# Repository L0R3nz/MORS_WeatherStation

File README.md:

# M.O.R.S.

This weather station is a passion-driven open-source project aimed at providing accurate monitoring of atmospheric conditions. Please note that as a hobby project, it may contain errors or limitations in functionality. However, I will do my best to continuously improving and refining the station's capabilities.

# Links
1. [Project Requirements](doc/Requirements.md)
2. [Sensors Evaluation](doc/Sensors.md)
3. [Hardware Documentation](doc/Hardware.md)

______________________________________________________
M.O.R.S project is based on opensource [tools](doc/Tools.md)

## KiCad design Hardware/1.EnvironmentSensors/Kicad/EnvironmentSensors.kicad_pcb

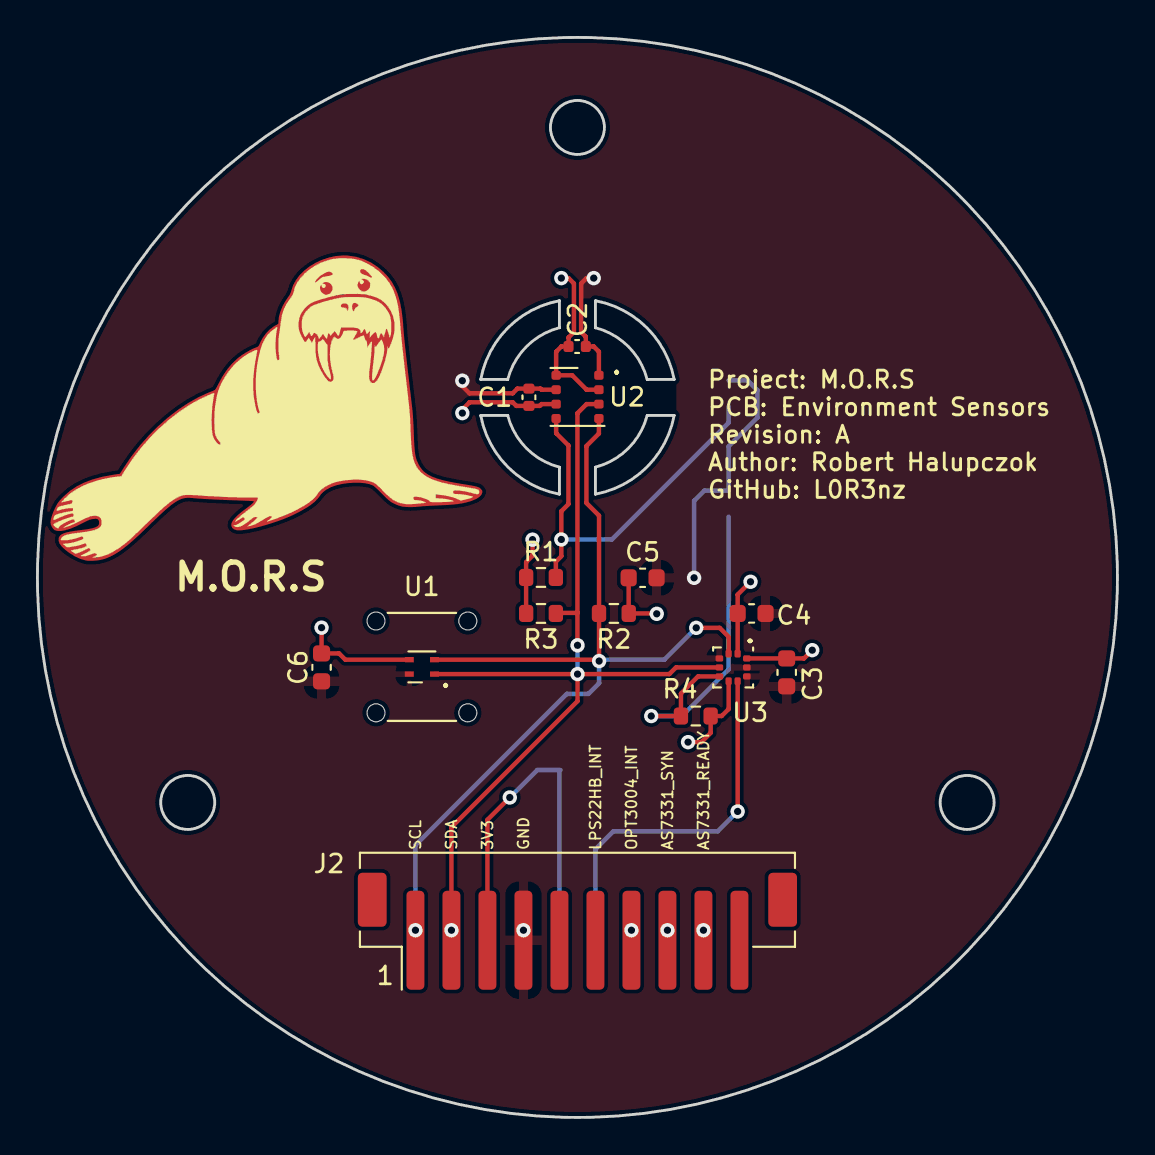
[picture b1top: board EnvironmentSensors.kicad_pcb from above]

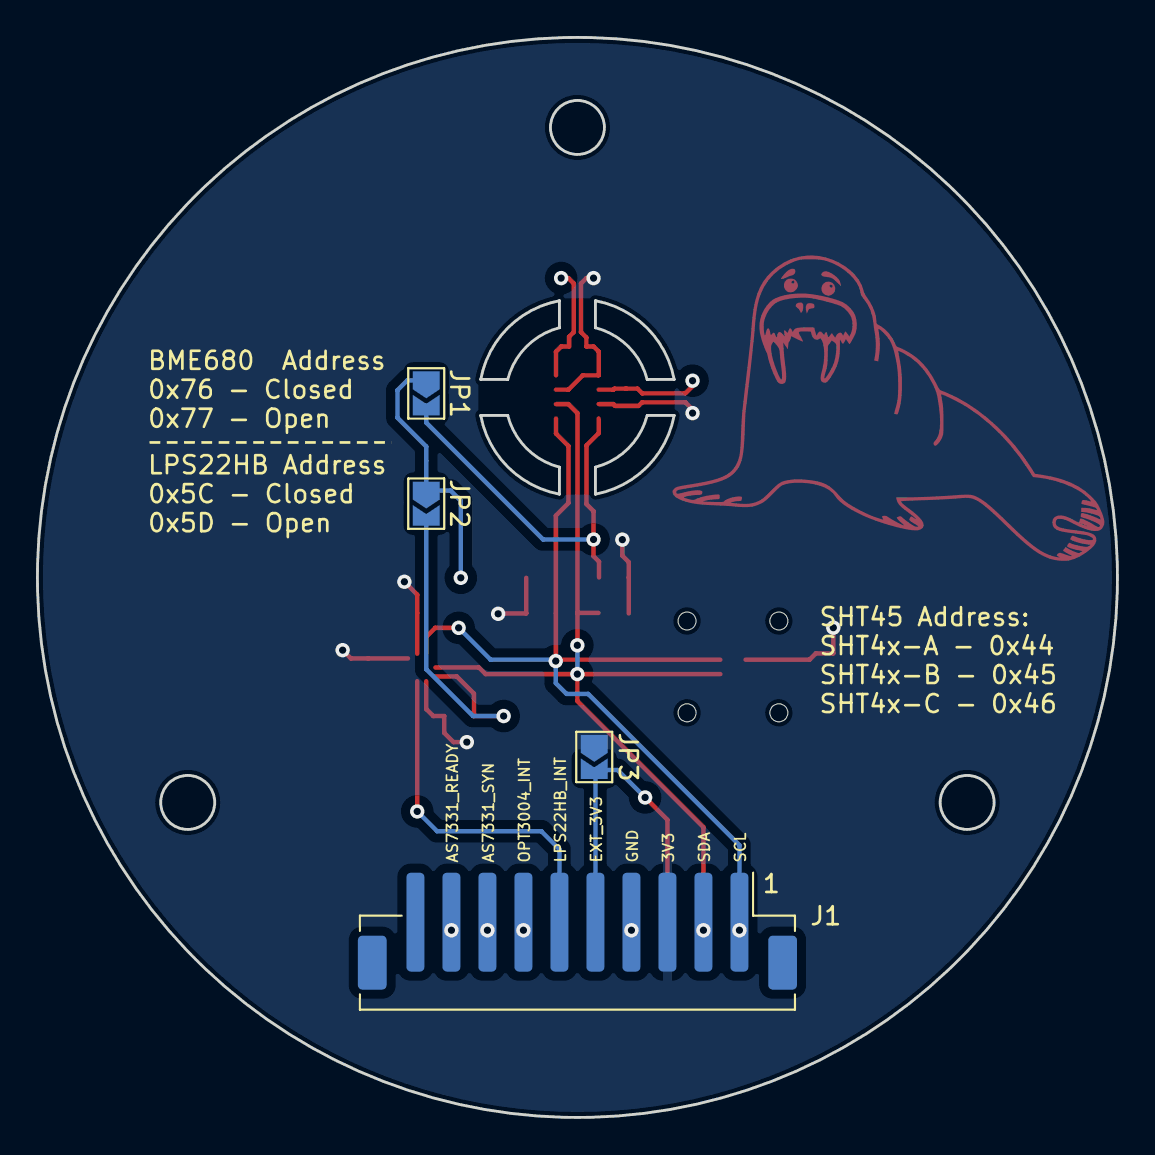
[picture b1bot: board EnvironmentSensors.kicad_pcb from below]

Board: 2 copper layers, 60.0 x 60.0 mm, 19 parts (4 on the bottom side), 11 nets.

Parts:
C1, C2: 100n; C_0402_1005Metric
C3, C5, C6: 100n; C_0603_1608Metric
C4: 4.7uF; C_0603_1608Metric
FL1: Sht45 Filter; FIL_SF2_FILTER_CAP
J1, J2: Conn_01x10_Pin; JST_PH_B10B-PH-SM4-TB_1x10-1MP_P2.00mm_Vertical
JP1, JP2, JP3: SolderJumper_2_Open; SolderJumper-2_P1.3mm_Open_TrianglePad1.0x1.5mm
R1, R4: 10k; R_0603_1608Metric
R2, R3: 4.7k; R_0603_1608Metric
U1: SHT4x; Sensirion_DFN-4_1.5x1.5mm_P0.8mm_SHT4x_NoCentralPad
U2: BME680; Bosch_LGA-8_3x3mm_P0.8mm_ClockwisePinNumbering
U3: LPS22HB; ST_HLGA-10_2x2mm_P0.5mm_LayoutBorder3x2y

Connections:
+3.3V: C1.1, C2.1, C3.1, C4.1, C5.1, C6.1, J1.3, JP3.1 (A), R1.1, R2.1, R3.2, R4.1, U1.3 (VDD), U2.2 (CSB), U2.6 (VDDIO), U2.8 (VDD), U3.1 (Vdd_IO), U3.6 (~CS), U3.10 (VDD)
EXT_3V3: J1.5, J2.3, JP3.2 (B)
EXT_AS7331_READY: J1.9, J2.9
EXT_AS7331_SYN: J1.8, J2.8
EXT_OPT3004_INT: J1.7, J2.7
GND: C1.2, C2.2, C3.2, C4.2, C5.2, C6.2, J1.4, J2.4, JP1.1 (A), JP2.1 (A), U1.4 (VSS), U2.1 (GND), U2.7 (GND), U3.3 (RES), U3.8 (GND), U3.9 (GND)
I2C_SCL: J1.1, J2.1, R2.2, U1.2 (SCL), U2.4 (SCK), U3.2 (SCL)
I2C_SDA: J1.2, J2.2, R3.1, U1.1 (SDA), U2.3 (SDI), U3.4 (SDA)
LPS22HB_INT: J1.6, U3.7 (INT_DRDY)
unnamed: JP1.2 (B), R1.2, U2.5 (SDO)
unnamed: JP2.2 (B), R4.2, U3.5 (SA0)

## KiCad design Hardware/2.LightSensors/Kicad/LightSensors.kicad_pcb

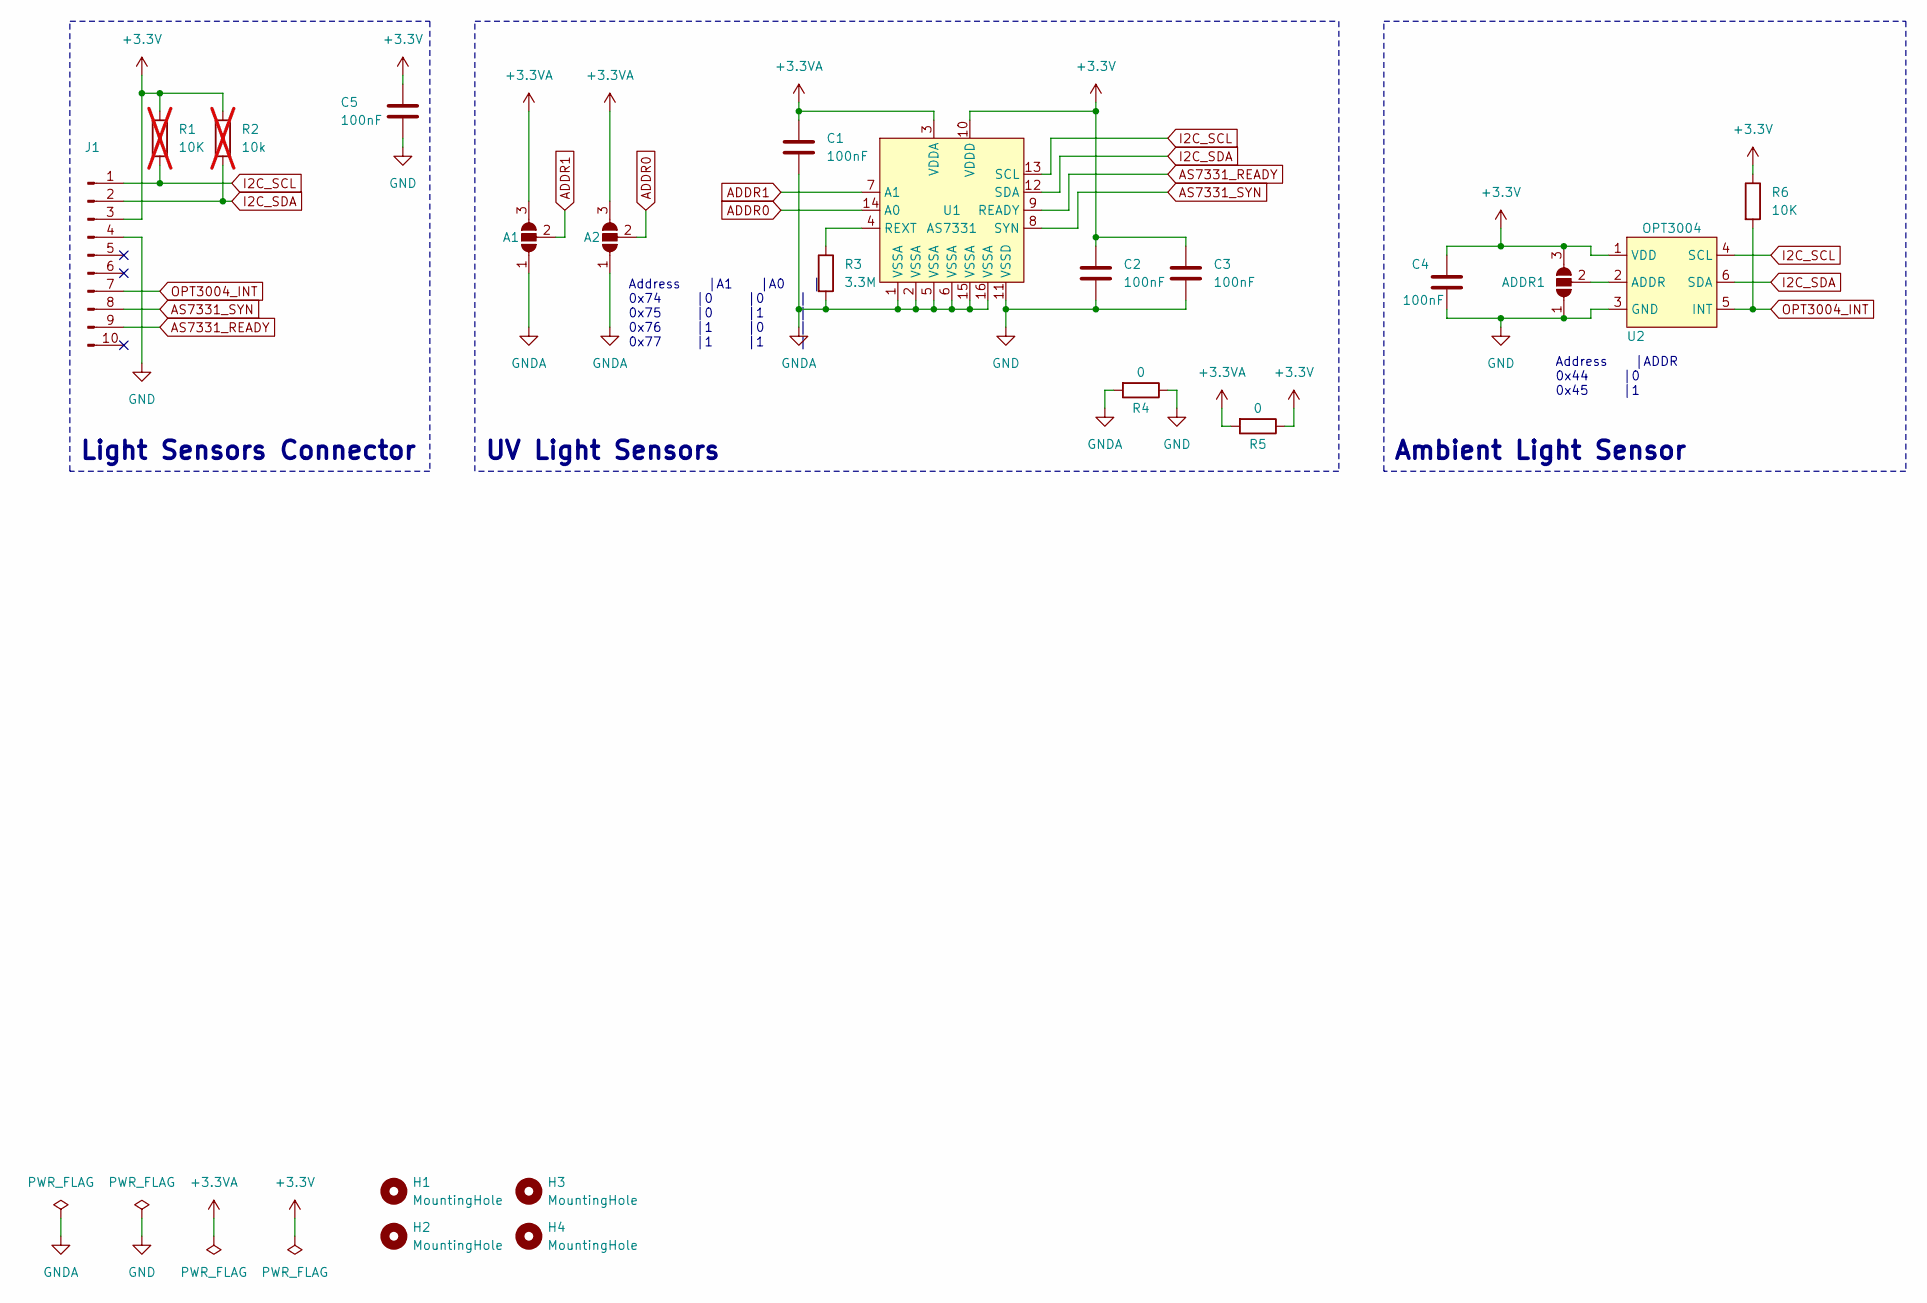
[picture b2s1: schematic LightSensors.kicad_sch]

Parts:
A1, A2: SolderJumper_3_Open; SolderJumper-3_P2.0mm_Open_TrianglePad1.0x1.5mm
ADDR1: SolderJumper_3_Open; SolderJumper-3_P2.0mm_Open_TrianglePad1.0x1.5mm
C1, C2, C3, C4, C5: 100nF; C_0603_1608Metric
H1, H2, H3, H4: MountingHole; MountingHole_2.2mm_M2
J1: Conn_01x10_Pin; JST_PH_B10B-PH-SM4-TB_1x10-1MP_P2.00mm_Vertical
R1: 10K; R_0603_1608Metric; not fitted
R2: 10k; R_0603_1608Metric; not fitted
R3: 3.3M; R_0603_1608Metric
R4, R5: 0; NetTie-2_THT_Pad0.3mm
R6: 10K; C_0603_1608Metric
U1: AS7331; OLGA-16
U2: OPT3004; SON65P200X200X65-7N

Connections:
+3.3V: ADDR1.3 (B), C2.1, C3.1, C4.1, C5.1, J1.3, R1.1, R2.1, R5.1, R6.1, U1.10 (VDDD), U2.1 (VDD)
+3.3VA: A1.3 (B), A2.3 (B), C1.1, R5.2, U1.3 (VDDA)
ADDR0: A2.2 (C), U1.14 (A0)
ADDR1: A1.2 (C), U1.7 (A1)
AS7331_READY: J1.9, U1.9 (READY)
AS7331_SYN: J1.8, U1.8 (SYN)
GND: ADDR1.1 (A), C2.2, C3.2, C4.2, C5.2, J1.4, R4.1, U1.11 (VSSD), U2.3 (GND)
GNDA: A1.1 (A), A2.1 (A), C1.2, R3.2, R4.2, U1.1 (VSSA), U1.2 (VSSA), U1.5 (VSSA), U1.6 (VSSA), U1.15 (VSSA), U1.16 (VSSA)
I2C_SCL: J1.1, R1.2, U1.13 (SCL), U2.4 (SCL)
I2C_SDA: J1.2, R2.2, U1.12 (SDA), U2.6 (SDA)
unnamed: ADDR1.2 (C), U2.2 (ADDR)
unnamed: R3.1, U1.4 (REXT)
OPT3004_INT: J1.7, R6.2, U2.5 (INT)

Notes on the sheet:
Light Sensors Connector
Address |A1 |A0 | 0x74 |0 |0 | 0x75 |0 |1 | 0x76 |1 |0 | 0x77 |1 |1 |
UV Light Sensors
Ambient Light Sensor
Address |ADDR 0x44 |0 0x45 |1

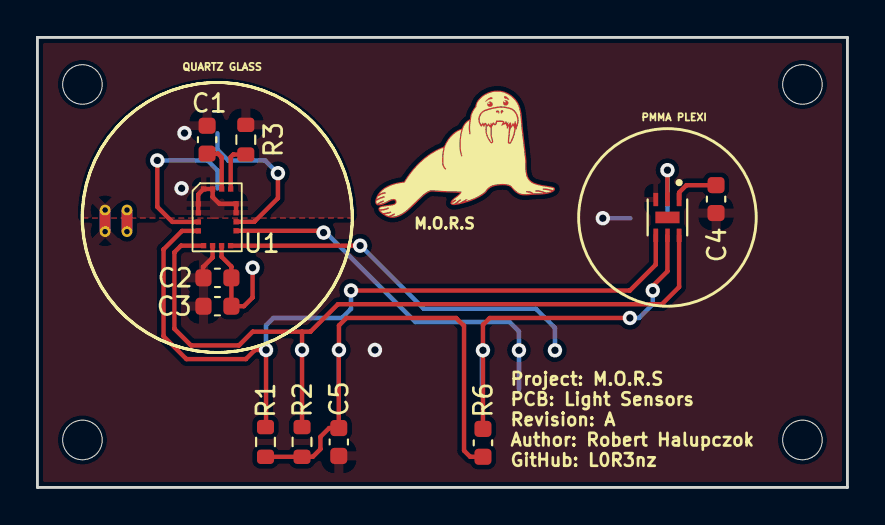
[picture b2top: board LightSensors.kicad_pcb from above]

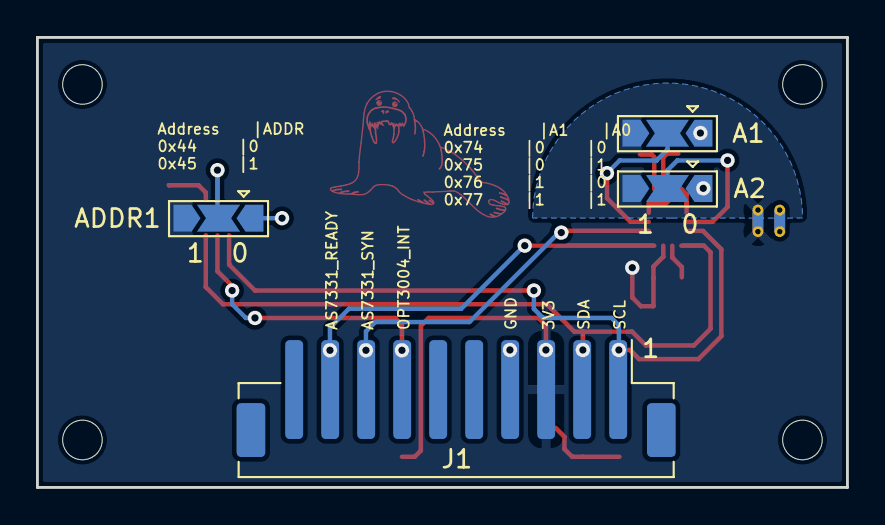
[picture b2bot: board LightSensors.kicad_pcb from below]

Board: 2 copper layers, 45.0 x 25.0 mm, 21 parts (5 on the bottom side), 13 nets.

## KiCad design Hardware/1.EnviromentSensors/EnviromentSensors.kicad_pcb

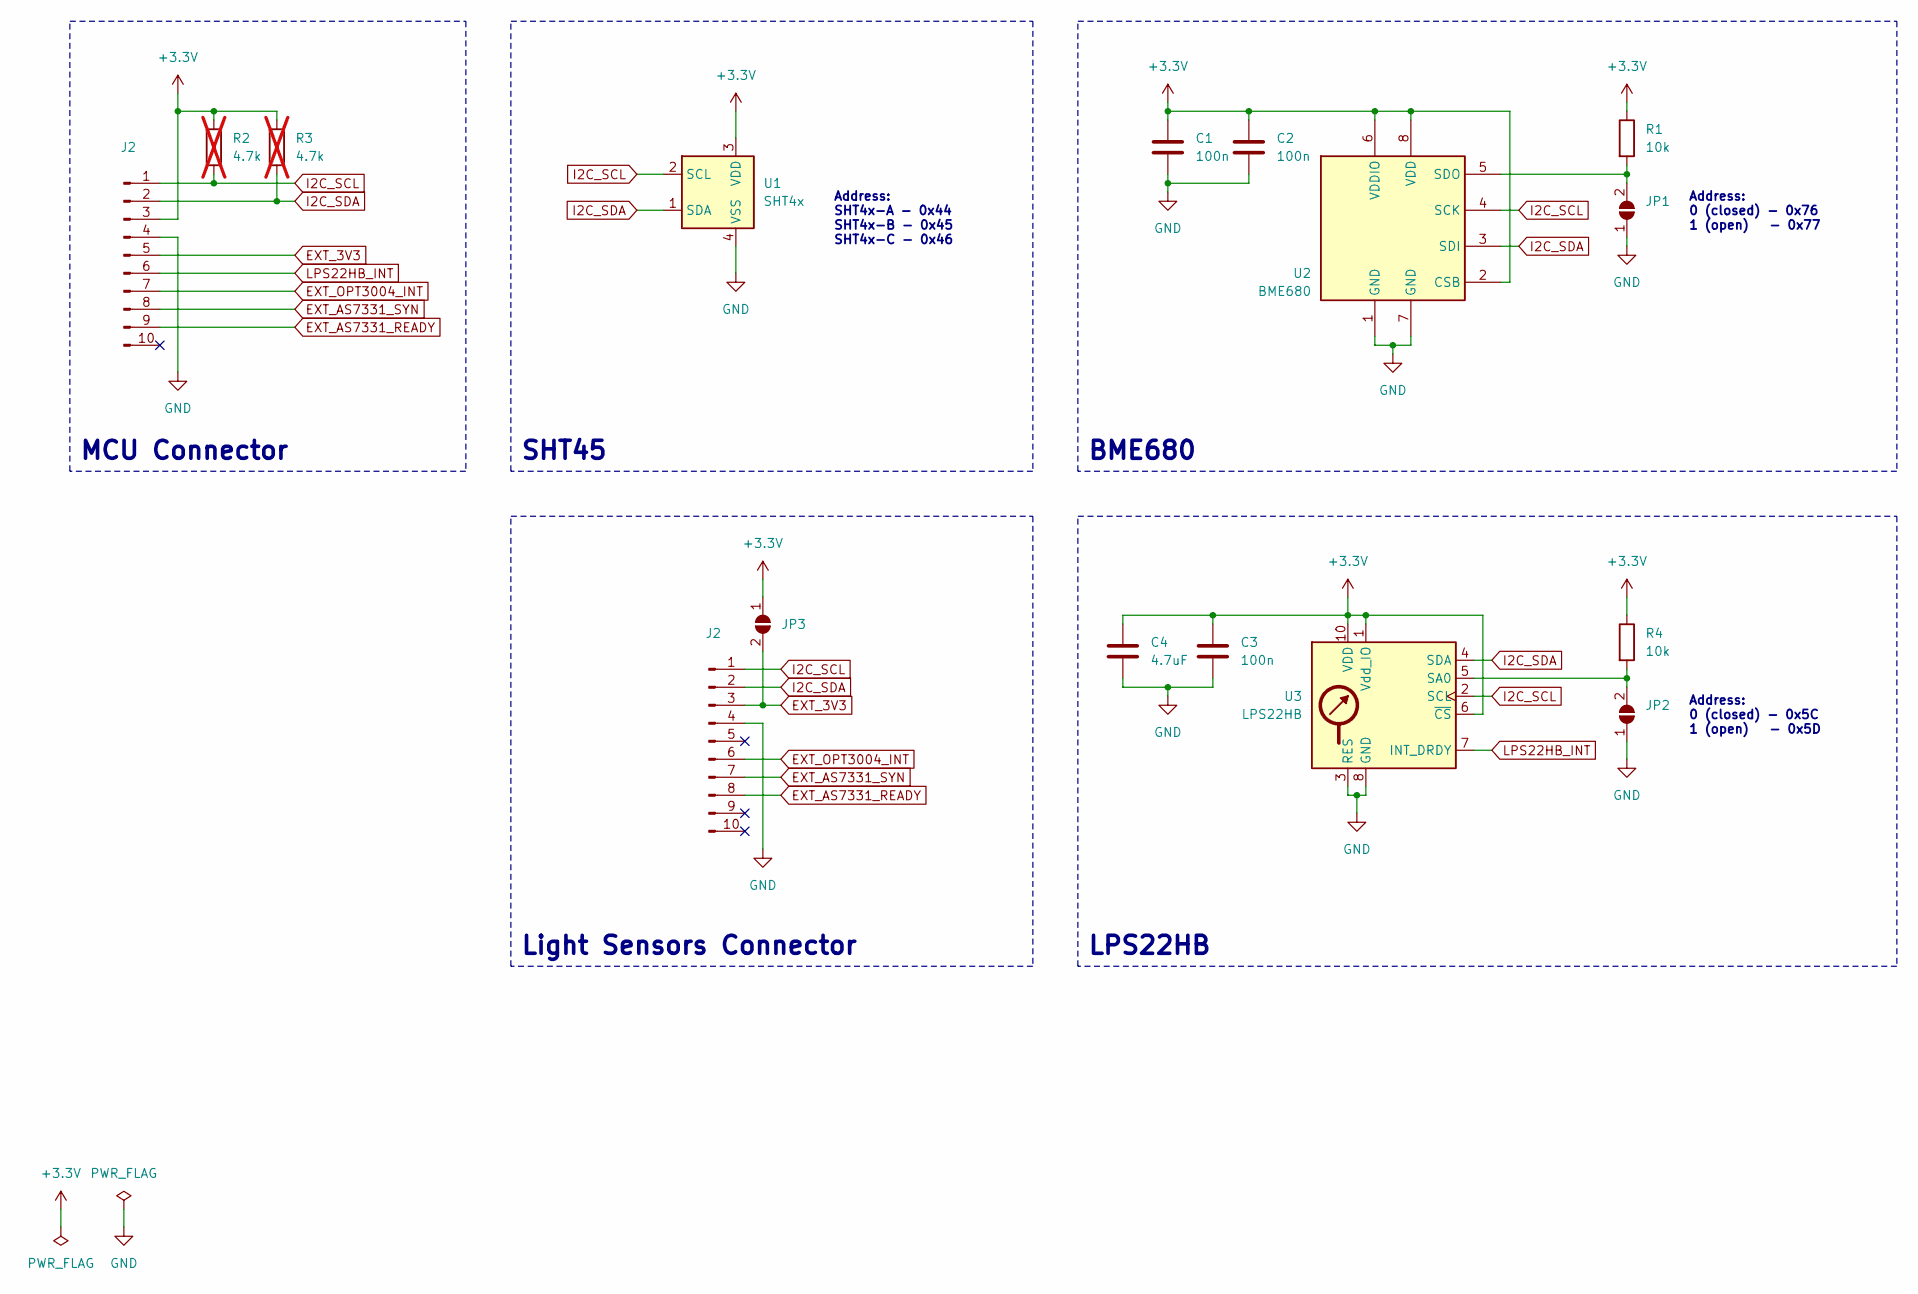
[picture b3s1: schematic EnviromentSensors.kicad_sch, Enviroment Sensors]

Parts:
C1, C2, C3: 100n; C_0402_1005Metric; MPN C77020
C4: 4.7uF; C_0402_1005Metric; MPN C2858031
J2: Conn_01x10_Pin; JST_PH_B10B-PH-K_1x10_P2.00mm_Vertical
JP1, JP2, JP3: SolderJumper_2_Open; SolderJumper-2_P1.3mm_Open_TrianglePad1.0x1.5mm
R1, R4: 10k; R_0402_1005Metric; MPN C25744
R2, R3: 4.7k; R_0402_1005Metric; MPN C25940; not fitted
U1: SHT4x; Sensirion_DFN-4_1.5x1.5mm_P0.8mm_SHT4x_NoCentralPad
U2: BME680; Bosch_LGA-8_3x3mm_P0.8mm_ClockwisePinNumbering; MPN C125972
U3: LPS22HB; ST_HLGA-10_2x2mm_P0.5mm_LayoutBorder3x2y; MPN C94049

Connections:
+3.3V: C1.1, C2.1, C3.1, C4.1, JP3.1 (A), R1.1, R2.1, R3.2, R4.1, U1.3 (VDD), U2.2 (CSB), U2.6 (VDDIO), U2.8 (VDD), U3.1 (Vdd_IO), U3.6 (~CS), U3.10 (VDD); also elsewhere on the board
EXT_3V3: JP3.2 (B); also elsewhere on the board
GND: C1.2, C2.2, C3.2, C4.2, JP1.1 (A), JP2.1 (A), U1.4 (VSS), U2.1 (GND), U2.7 (GND), U3.3 (RES), U3.8 (GND), U3.9 (GND); also elsewhere on the board
I2C_SCL: R2.2, U1.2 (SCL), U2.4 (SCK), U3.2 (SCL); also elsewhere on the board
I2C_SDA: R3.1, U1.1 (SDA), U2.3 (SDI), U3.4 (SDA); also elsewhere on the board
LPS22HB_INT: U3.7 (INT_DRDY); also elsewhere on the board
unnamed: JP1.2 (B), R1.2, U2.5 (SDO)
unnamed: JP2.2 (B), R4.2, U3.5 (SA0)

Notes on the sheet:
Address: 0 (closed) - 0x76 1 (open) - 0x77
Address: 0 (closed) - 0x5C 1 (open) - 0x5D
Address: SHT4x-A - 0x44 SHT4x-B - 0x45 SHT4x-C - 0x46
MCU Connector
BME680
LPS22HB
SHT45
Light Sensors Connector

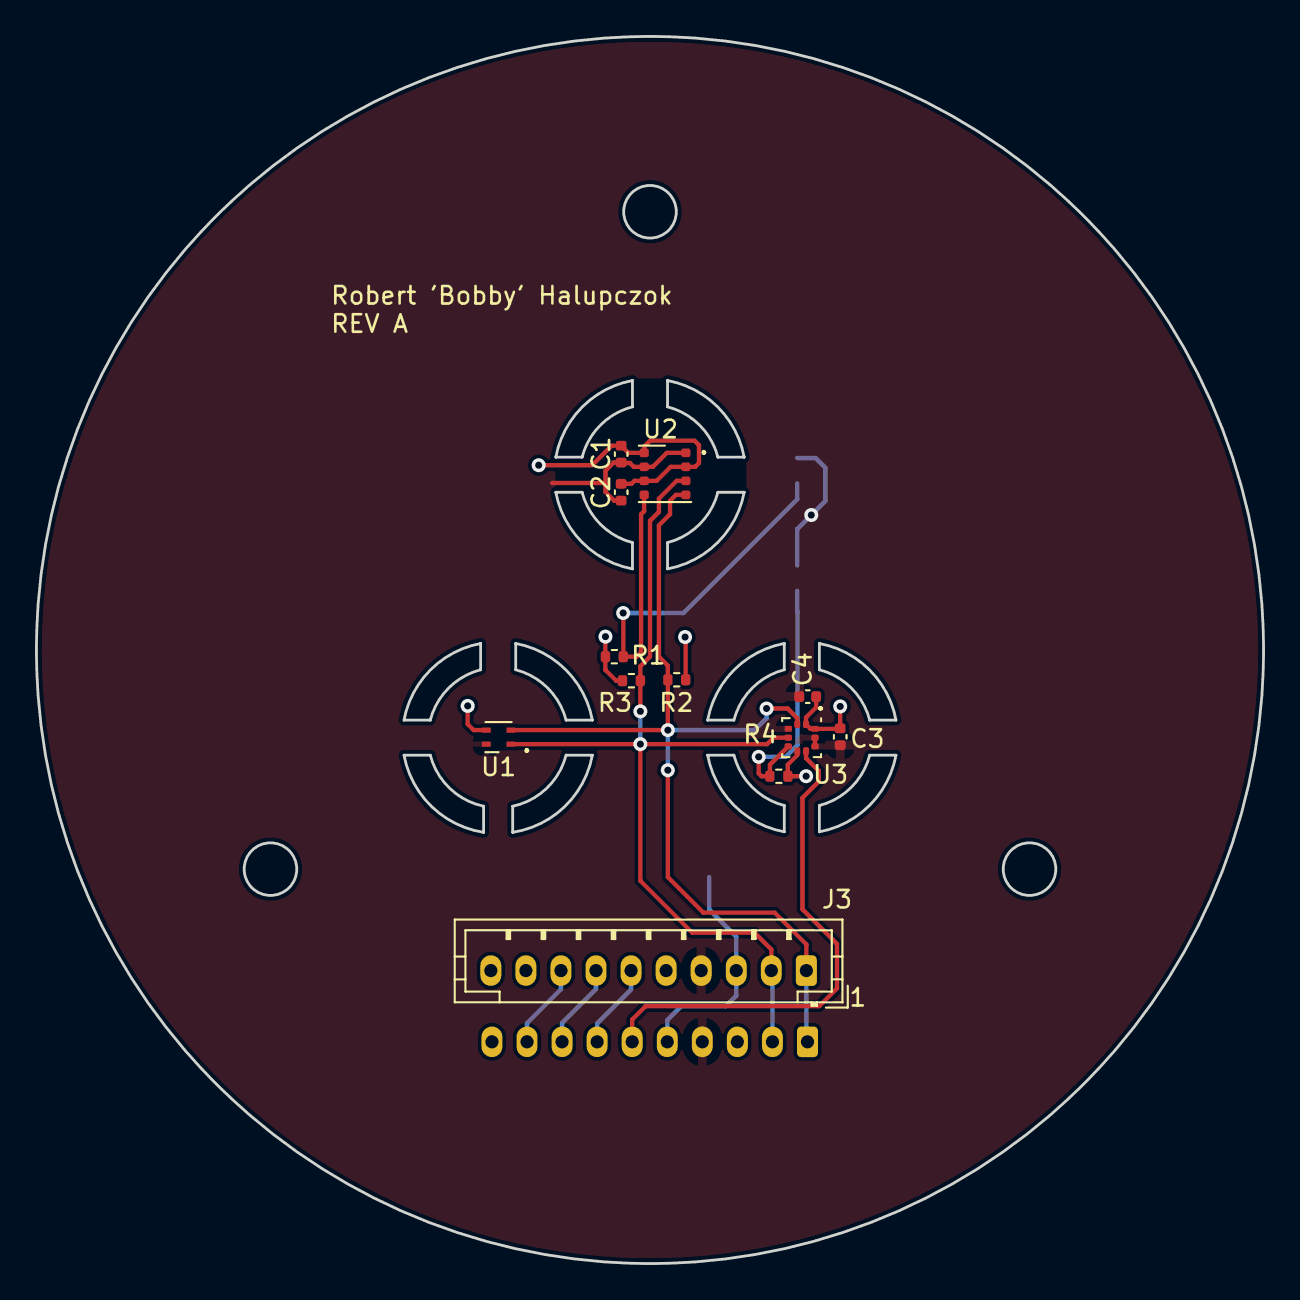
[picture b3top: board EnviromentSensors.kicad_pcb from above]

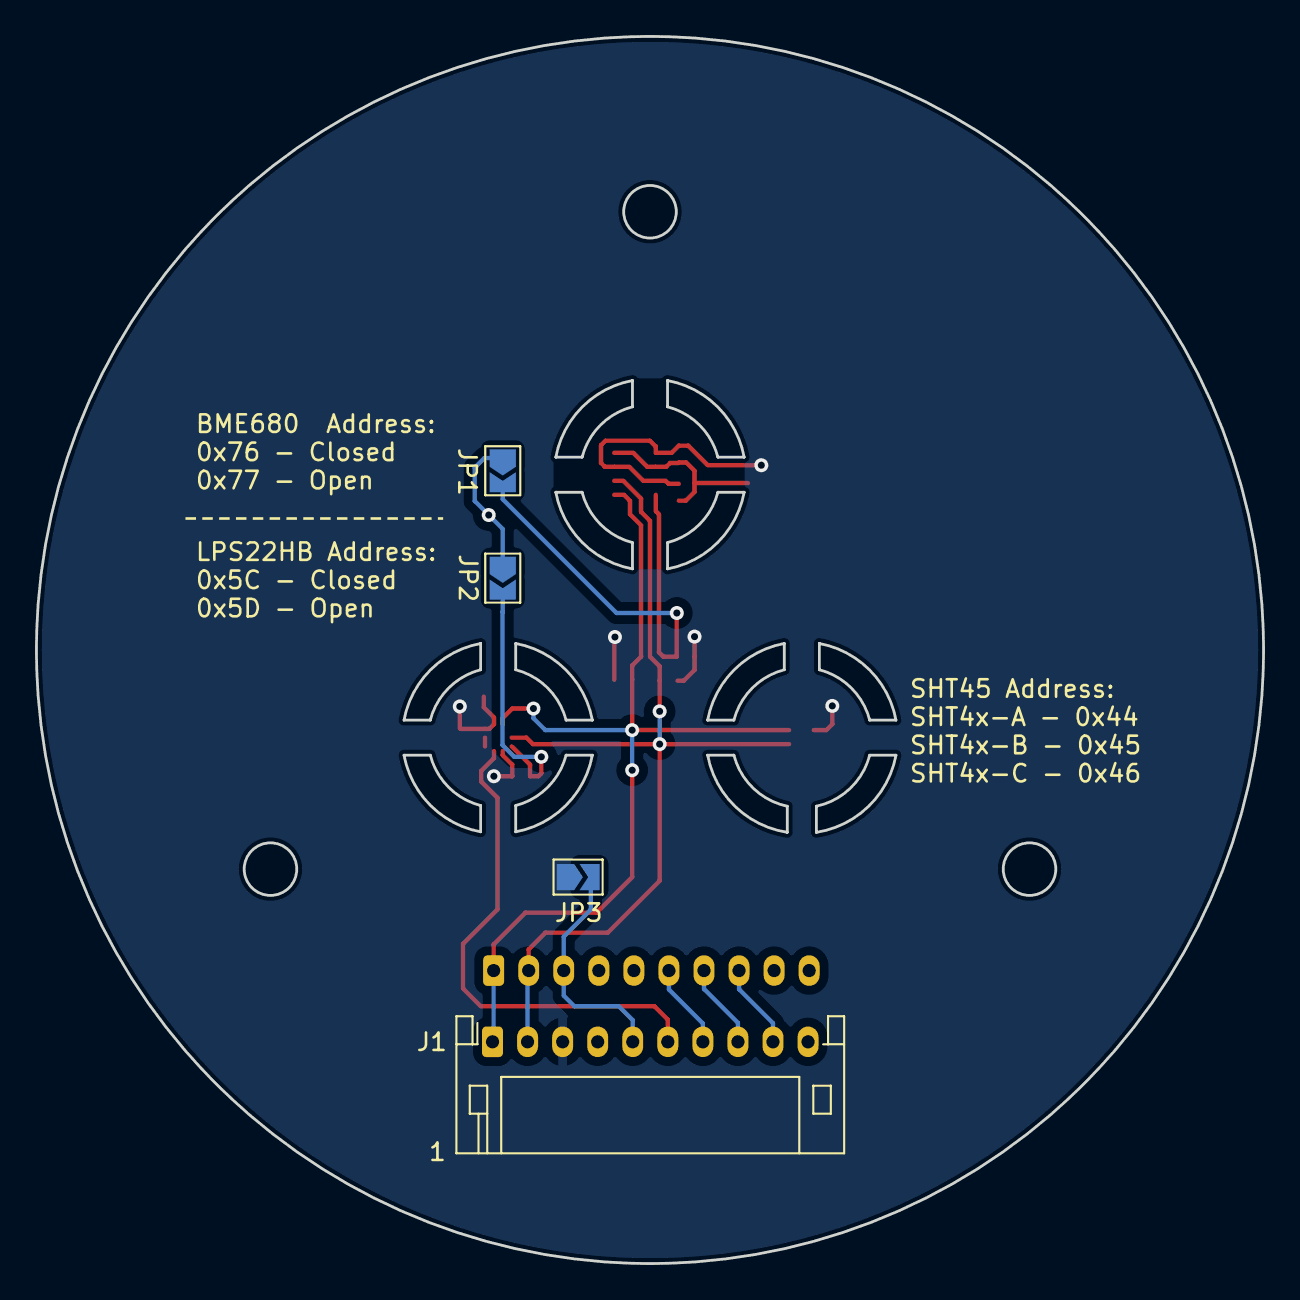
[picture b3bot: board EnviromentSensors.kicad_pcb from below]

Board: 2 copper layers, 70.0 x 70.0 mm, 16 parts (4 on the bottom side), 11 nets.

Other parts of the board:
J1: Conn_01x10_Pin; JST_PH_S10B-PH-K_1x10_P2.00mm_Horizontal
J3: Conn_01x10_Pin; JST_PH_B10B-PH-K_1x10_P2.00mm_Vertical

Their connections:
+3.3V: J1.3; also elsewhere on the board
EXT_3V3: J1.5, J3.3; also elsewhere on the board
EXT_AS7331_READY: J1.9, J3.8
EXT_AS7331_SYN: J1.8, J3.7
EXT_OPT3004_INT: J1.7, J3.6
GND: J1.4, J3.4; also elsewhere on the board
I2C_SCL: J1.1, J3.1; also elsewhere on the board
I2C_SDA: J1.2, J3.2; also elsewhere on the board
LPS22HB_INT: J1.6; also elsewhere on the board

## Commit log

2023-07-13 Add initial project requirements for sensors
2023-07-13 Specify requirements for system, hardware, sensors and enclosure
2023-07-14 Move requirements into separate file
2023-07-16 Add Sensors Diagram
2023-07-16 Add Temperature / Humidity / Preasure sensors section
2023-07-16 Add light sensors section
2023-07-16 Update Light sensors table
2023-07-17 Update Readme by adding sensors evaluation document
2023-07-17 Add .gitignore rules for kicad
2023-07-17 Add schematic for Sensor PCB
2023-07-17 Change pullup resistor from 10k to 4.7k
2023-07-17 Fill revision and schematic date fields
2023-07-17 Add Power flag to solve ECR errors
2023-07-17 Assign footprint for schematic elements
2023-07-17 Add 3d Models for sensors
2023-07-19 Add initial bord file
2023-07-19 Add KiCad DRC rules for JLCPCB
2023-07-21 Change resistors and capasitors footprint from 0201 to 0402
2023-07-21 Add initial version of Enviromental Sensors PCB
2023-07-22 Add LCSC part numbers for electronic components
2023-07-22 Update 3d models for sensors
2023-07-23 Change PCB design
2023-07-23 Add FreeCAD file with PCB model
2023-07-23 Add gitignore
2023-07-23 Update project settings
2023-07-28 Create KiCad project for LightSensors PCB
2023-07-28 Import Schematic and PCB settings from EnviromentSensors Board
2023-07-28 Add JLCPCB Design Rules
2023-07-28 Add AS7331 Library
2023-07-28 Add AS7331 symbol to project library table
2023-07-28 Add AS7331 footprint to project library table
2023-07-28 Add basic schematic version
2023-07-28 Create OPT3004 Symbol
2023-07-28 Add OPT3004 footprint to project library table
2023-07-28 Add OPT3004 into schematic
2023-07-28 Add Footprint and 3d model for OPT3004
2023-07-28 Add kicad lock files into gitignore
2023-07-28 Update OPT3004 symbol property
2023-07-28 Assign footprints
2023-07-28 Add OPT3004 datasheet file into docs
2023-07-28 Update schematic
2023-07-30 Add connector for LightSensors board
2023-07-30 Update PCB by adding connector for LightSensors board
2023-07-30 Update schematic for LightSensors PCB
2023-07-30 Change connector to JST PH 2.0
2023-07-30 Add update PCB dimension
2023-07-30 Change Ambient light sensor and fix spelling
2023-07-30 Rename Environmental Sensors board due to spelling
2023-07-30 Change folder structure
2023-07-30 Update 3d model of Environment Sensors PCB
2023-07-30 Update PCB for LightSensors
2023-08-05 Add footprint, symbol and 3d model for Sensirion SF2 filter
2023-08-05 Append footprint to project
2023-08-05 Append symbol to project
2023-08-05 Add SF2 filter to schematic
2023-08-05 Modify PCB layout
2023-08-05 Create InnerSection of solar radiation shield for sensors
2023-08-05 Add InnerSection stl file
2023-08-05 Create InnerSection whitch holds PCB
2023-08-05 Add PCB holder section STL file
2023-08-05 Create TopSection of solar radiation shield for sensors
2023-08-05 Add TopSection STL file
2023-08-05 Create BottomSection of solar radiation shield for sensors
2023-08-05 Add BottomSection STL file
2023-08-05 Create RadiationShield assembly
2023-08-05 Add Assembly STL file
2023-08-14 modify top section of radfiation shield to have initial dimentions od light sensor PCB
2023-08-14 update footprints
2023-08-14 Design initial version of PCB for light sensors
2023-08-14 Update assembly to check collisions
2023-08-20 Add signal names on silkscreen and add connector 3dmodel
2023-08-20 Archive all 3d models used in pcb
2023-08-20 Update pcb due to connector pinout fix
2023-08-20 Backup 3d models of components
2023-08-20 Change footprint for connectors
2023-08-20 Update pcb due to conector change
2023-08-27 Add project logo
2023-08-27 Create kicad footprint with logo
2023-08-27 Append logo footprint into project table
2023-08-27 Add project logo and update silkscreen
2023-08-27 Update kicad logo footprint library
2023-08-27 add logo footprint library
2023-08-27 Fix 10mm footprint logo
2023-08-27 Add logo into pcb and update silkscreen
2023-08-27 Add logo to readme file
2023-08-27 Fix logo display
2023-08-27 Update Top Shield
2023-08-27 Add back cover for top shield to improve moisture resistance
2023-08-27 Recreate assembly
2023-08-27 Add external component for assembly
2023-08-27 Update assembly
2023-08-27 Update STL file for Top section
2023-08-27 Add STL file for new top section back cover
2023-08-27 Add gerber files for environmental sensors pcb
2023-08-27 Add gerber files for light sensors pcb
2023-08-27 Add iBOM for environmental sensors pcb
2023-08-27 Add iBOM for light sensors pcb
2023-08-27 Add schematic for light sensors board
2023-08-27 Add schematic for environmental sensors board
2023-08-27 Set default plot directory
2023-08-27 Add ibom config
2023-08-27 Update Gerber files
2023-08-27 Update iBOM files
2023-08-27 Update PCBs
2023-09-02 Add capacitor for supply connector, SHT21 and change resistors and capacitors footprint to 0603
2023-09-02 Update layout with changes made in schematic
2023-09-02 Change footprints for resistors, capasitors and change mounting holes to M2
2023-09-03 Add capacitor bettwen VCC and GND, Update schematic date
2023-09-03 Add capacitor bettwen VCC and GND on PCB
2023-09-03 Update schematic date
2023-09-03 Update iBom settings
2023-09-03 Generate iBom file
2023-09-03 Update schematic and change directory to doc folder
2023-09-03 Update gitignore by adding netlist.ipc files
2023-09-03 Add missing 3d model of lightSensors pcb
2023-09-03 Update 3d model of environmental sensors pcb
2023-09-03 Update assembly of radiation sheld
2023-09-03 Pre release environmental sensors PCB
2023-09-03 Pre release light sensors PCB
2023-09-04 Create kicad project
2023-09-04 Add library folder
2024-02-18 Update top element of the radiation sheield
2024-02-18 Update STL file for top section of radiation shield
2024-02-18 Update radiation shield assembly
2024-02-18 Add information about used tools
2024-02-18 Rearrange logo folder
2024-02-18 Rearrange images used for documentation
2024-02-18 Add hardware documentation for Environment sensors
2024-02-18 Add hardware documentation for Light sensors
2024-02-18 Add images of real boards
2024-08-14 Add stencil holder tool to improve soldering proccess
